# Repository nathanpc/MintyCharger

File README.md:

# MintyCharger

A very simple 9V (9.6V and 8.4V) NiMH charger based on a PIC microcontroller with a charge state indicator that fits neatly inside a Altoids tin.

## Schematic and Board Layout

A very simple topology, the PIC is generating a PWM pulse which is converted to a analog voltage by using a filter, which is fed into a op-amp that will be controlling the voltage. The current limit is set by the potentiometer `R10`. This is literally a miniature version of a primitive "lab" power supply.

As you can see the board is very tiny and is designed to fit inside a Altoids tin along side the battery that it will be charging.

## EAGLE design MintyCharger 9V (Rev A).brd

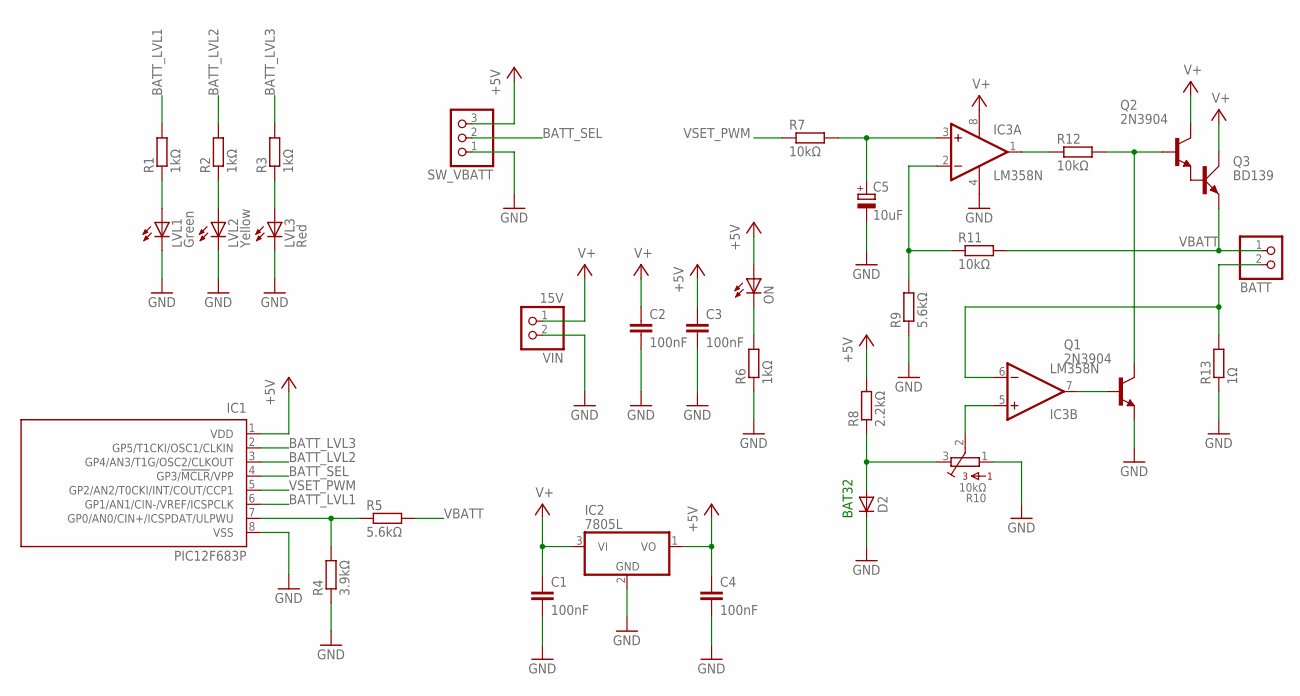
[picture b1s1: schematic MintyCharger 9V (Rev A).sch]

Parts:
BATT: JST_2PIN-THM; JST-PH-2-THM
C1, C2, C3, C4: 100nF; C025-025X050
C5: 10uF; E2,5-6
D2: 1N4148DO35-7; DO35-7
IC1: PIC12F683P; DIL8
IC2: 7805L; TO92
IC3: LM358N; DIL08
LVL1: Green; LED2X5
LVL2: Yellow; LED2X5
LVL3: Red; LED2X5
ON: LEDSQR2X5; LED2X5
Q1, Q2: 2N3904; TO92
Q3: BD139; TO126AV
R1, R2, R3, R6: 1kΩ; 0207/10
R4: 3.9kΩ; 0207/10
R5, R9: 5.6kΩ; 0207/10
R7, R11, R12: 10kΩ; 0207/10
R8: 2.2kΩ; 0207/10
R10: 10kΩ; 3362U
R13: 1Ω; 0207/10
SW_VBATT: PINHD-1X3; 1X03
VIN: 15V; JST-PH-2-THM

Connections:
+5V: C3.1, C4.1, IC1.1 (VDD), IC2.1 (VO), ON.A, R8.2, SW_VBATT.3
BATT_LVL1: IC1.6 (GP1/AN1/CIN-/VREF/ICSPCLK), R1.2
BATT_LVL2: IC1.3 (GP4/AN3/T1G/OSC2/CLKOUT), R2.2
BATT_LVL3: IC1.2 (GP5/T1CKI/OSC1/CLKIN), R3.2
BATT_SEL: IC1.4 (GP3/!MCLR!/VPP), SW_VBATT.2
GND: C1.2, C2.2, C3.2, C4.2, C5.-, D2.C, IC1.8 (VSS), IC2.2 (GND), IC3.4 (V-), LVL1.K (C), LVL2.K (C), LVL3.K (C), Q1.3 (E), R4.1, R6.1, R9.1, R10.1, R13.1, SW_VBATT.1, VIN.2 (1)
ISENSE: BATT.2 (1), IC3.6 (-IN), R13.2
unnamed: LVL1.A, R1.1
unnamed: IC3.2 (-IN), R9.2, R11.1
unnamed: IC3.1 (OUT), R12.1
unnamed: Q2.3 (E), Q3.B
unnamed: Q1.1 (C), Q2.2 (B), R12.2
unnamed: IC3.7 (OUT), Q1.2 (B)
unnamed: D2.A, R8.1, R10.3
unnamed: IC3.5 (+IN), R10.2
unnamed: IC1.7 (GP0/AN0/CIN+/ICSPDAT/ULPWU), R4.2, R5.1
unnamed: LVL2.A, R2.1
unnamed: LVL3.A, R3.1
unnamed: ON.K (C), R6.2
V+: C1.1, C2.1, IC2.3 (VI), IC3.8 (V+), Q2.1 (C), Q3.C, VIN.1 (2)
VBATT: BATT.1 (2), Q3.E, R5.2, R11.2
VOUT: C5.+, IC3.3 (+IN), R7.2
VSET_PWM: IC1.5 (GP2/AN2/T0CKI/INT/COUT/CCP1), R7.1

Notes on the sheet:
BAT32

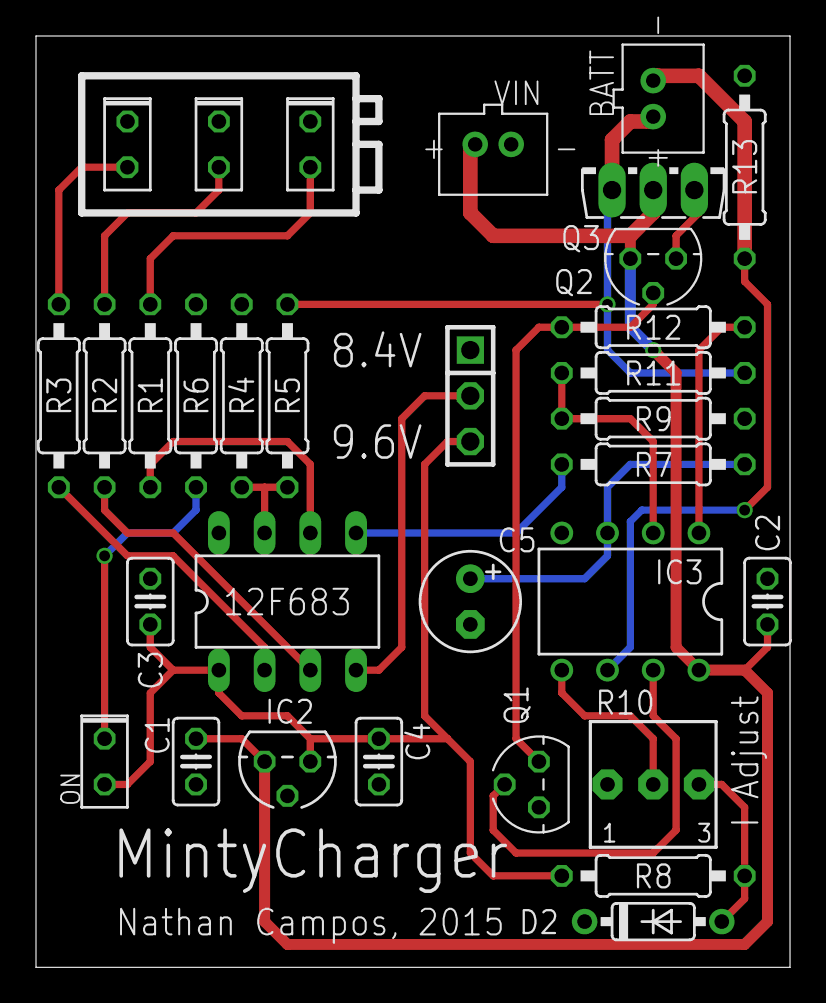
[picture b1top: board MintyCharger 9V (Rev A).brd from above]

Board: 4 copper layers, 41.9 x 51.7 mm, 32 parts (0 on the bottom side), 23 nets.

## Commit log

2015-05-02 Moved BATT_SEL to GP3
2015-05-02 Added the PIC code
2017-02-04 A bunch of stuff I forgot to commit a very long time ago
